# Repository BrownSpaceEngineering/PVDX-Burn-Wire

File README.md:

# BurnWire

Burn-wire release board for the PVDX CubeSat. Generates a constant current of 1.6A through a nichrome wire to sever the retention line holding deployable camera arm in its stowed position.

## Status
- Design phase: manufactured (rev-3.1 sent to fab 2026-08-22)
- Current rev: rev-3.1
- Contributors: Atharv Chowdhary, Nick Cavallo, Jayla Hsiung, Emily Zhang, Kelly Lin, Natalie Cavallo, Misha Zinchuk

## System overview

BurnWire was originally forked from another team's Altium-designed board and imported into KiCad, which is the source of most of the quirks documented below. 

**WIP**
Known components on the board (confirmed via schematic/PCB library references, not yet mapped to a full circuit description — fill in as this gets documented properly):

- **ADP2303ARDZ** — synchronous step-down switching regulator. Per standing design notes, this part needs a Schottky diode (e.g. BAT54, here likely the placed **B330B-13-F**) from V_in to the BST pin to prevent bootstrap collapse at 5V input (datasheet Figure 48) — worth confirming this placement is present and correctly oriented.
- **B330B-13-F** — Schottky diode, SMB package (3 footprint variants exist in `libs/footprints.pretty/`: base, `-M`, `-L`; the placed instance uses `-L`).
- **IND_NLV32T_TDK** (TDK NLV32T-3R3J-EF, 3.3µH) and **Bourns SRN6045** — two inductor footprints present; [confirm: both used in the regulator stage, or does one serve the burn-wire drive circuit?]
- **JST B6B-XH-A** 6-pin connector — external interface (power / command / burn-wire line — confirm pinout).
- 0.25Ω 3W power resistor (2512/2010 footprint) — likely current-sense or burn-wire load-adjacent; confirm function.
- Standard passives: 0603/0805 resistors, 0603 100nF decoupling caps, WCAP-ASLI 5x5.5mm bulk electrolytic.
- Test points inherited from the original board's library (`PowerManagmentBoard_V4.0:TP` nickname — currently orphaned, see Open Items).

### Repo layout
```
BurnWire/
├── BurnWire.kicad_pro / .kicad_sch / .kicad_pcb / .step
├── LTSpice_burnWire.asc
├── fp-lib-table, sym-lib-table
├── libs/
│   ├── footprints.pretty/
│   └── symbols/
└── manufacturing/
    └── rev-1_2026-08-22/
        └── gerbers/
```
No schematics/, spice/, or tools/ directories — the LTSpice simulation is currently stored at the repository root as LTSpice_burnWire.asc.

## Key design notes
- **Inherited from Altium, not yet fully re-linked in KiCad.** Nearly every custom part on the schematic (`Burn Wire Dev Board-altium-import:*`, `Burn Wire Dev Board:root_N_*`, `PowerManagmentBoard_V4.0:*`) has no corresponding entry in `sym-lib-table`. The schematic still opens and renders correctly because KiCad caches each symbol's full geometry inline at placement time — `sym-lib-table` is only consulted when re-editing or re-placing a symbol. Don't take "it opens fine" as evidence the library links are healthy.
- **PCB layer names are non-standard**, carried over from the Altium import (e.g. `Mechanical 1/5/7/13/15`, `User.2/3/4` instead of KiCad's standard `Margin`/`User.Comments`/etc.). Not remapped in this reorg — flagged as a full production-file redo for later, out of scope for repo hygiene.
- **ADP2303 bootstrap diode** — see System overview above; this is a known failure mode for this regulator at 5V input, worth double-checking against the datasheet if this board is ever re-spun.
- `libs/symbols/` now holds four properly filed vendor symbols (B330B-13-F, B6B-XH-A_LF__SN_, NLV32T-3R3J-EF, WCAP-ASLI_5X5.5), but **none are currently referenced by the schematic** — the placed parts use generic `Device:`/`Connector:` symbols instead. These are available for future use, not currently wired in.

## Simulations
- `LTSpice_burnWire.asc` — LTSpice simulation of the burn-wire constant-current regulator.

## Manufacturing history
| Rev | Date | Notes | Location |
|-----|------|-------|----------|
| 3.1 | 2026-08-22 | First fab | `manufacturing/rev-1_2026-08-22/gerbers/` |

## Open items / TBD
- PCB layer names still reflect the Altium import (`Mechanical 1/5/7/13/15`, `User.2/3/4`) — needs remapping to standard KiCad layers as part of a full production-file redo.
- `burn_wire:CR_SMB_320-345BE_DIO-L` and `burn_wire:IND_BOURNS_SRN6045` footprint nicknames on the PCB aren't yet re-linked to the `footprints` library in `fp-lib-table` — the backing files exist in `libs/footprints.pretty/` now, they just need the reference updated.
- `Burn Wire Dev Board:0603` and `PowerManagmentBoard_V4.0:TP` footprint nicknames have no backing file anywhere in the repo — genuinely missing, not just unlinked.
- Most schematic symbols are unlinked from `sym-lib-table` (see Key design notes) — re-linking or rebuilding these is a real schematic-level task, not a file move.
- The placed `burn_wire:CR_SMB_320-345BE_DIO-L` instance has a pad offset that doesn't cleanly match either library copy of that footprint (hand-nudged geometry) — worth a visual QC pass against the fabbed rev-1 board.

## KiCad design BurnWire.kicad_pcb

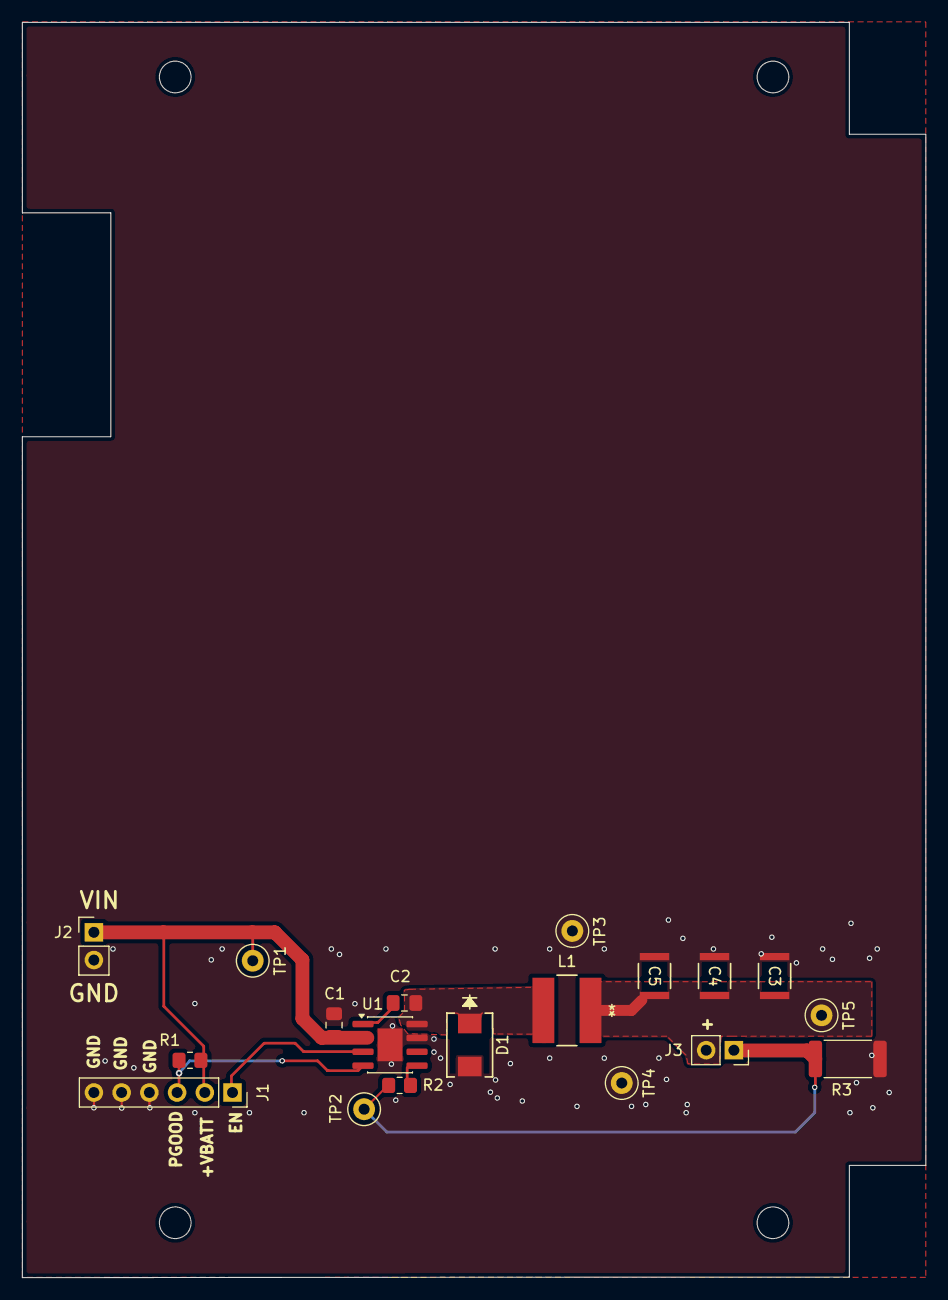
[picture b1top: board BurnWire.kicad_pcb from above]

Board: 2 copper layers, 82.8 x 115.0 mm, 19 parts (0 on the bottom side), 9 nets.

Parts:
C1: 22u; C_0805_2012Metric_Pad1.18x1.45mm_HandSolder
C2: 0.1u; C_0805_2012Metric_Pad1.18x1.45mm_HandSolder
C3, C4, C5: 47uF; CAP_GRM_32E_MUR
D1: B330B-F; CR_SMB_320-345BE_DIO-L
J1: Conn_01x06_Pin; PinSocket_1x06_P2.54mm_Vertical
J2: Conn_01x02_Pin; PinHeader_1x02_P2.54mm_Vertical
J3: Conn_01x02_Pin; PinSocket_1x02_P2.54mm_Vertical
L1: 3.3u; IND_BOURNS_SRN6045
R1, R2: 10k; R_0805_2012Metric_Pad1.20x1.40mm_HandSolder
R3: 0.5R; R_2512_6332Metric
TP1, TP2, TP3, TP4, TP5: TP; TestPoint_Loop_D1.80mm_Drill1.0mm_Beaded
U1: ADP2303ARDZ; SOIC-8-1EP_3.9x4.9mm_P1.27mm_EP2.29x3mm

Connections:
+VBATT: C1.1, J1.2, J2.1, R1.2, TP1.1 (1_1), U1.2 (Vin)
/BURN_NEG: J3.1, R2.2, R3.2, TP2.1 (1_1)
/BURN_POS: C3.2, C4.2, C5.2, J3.2, L1.1, TP5.1 (1_1)
/ENABLE: J1.1, U1.3 (EN)
/FB: R2.1, U1.5 (FB)
/PGOOD: J1.3, R1.1, U1.4 (PGOOD)
GND: C1.2, C3.1, C4.1, C5.1, D1.2 (A), J1.4, J1.5, J1.6, J2.2, R3.1, TP3.1 (1_1), TP4.1 (1_1), U1.7 (GND), U1.9 (PADGND)
unnamed: C2.1, D1.1 (K), L1.2, U1.8 (SW)
unnamed: C2.2, U1.1 (BST)

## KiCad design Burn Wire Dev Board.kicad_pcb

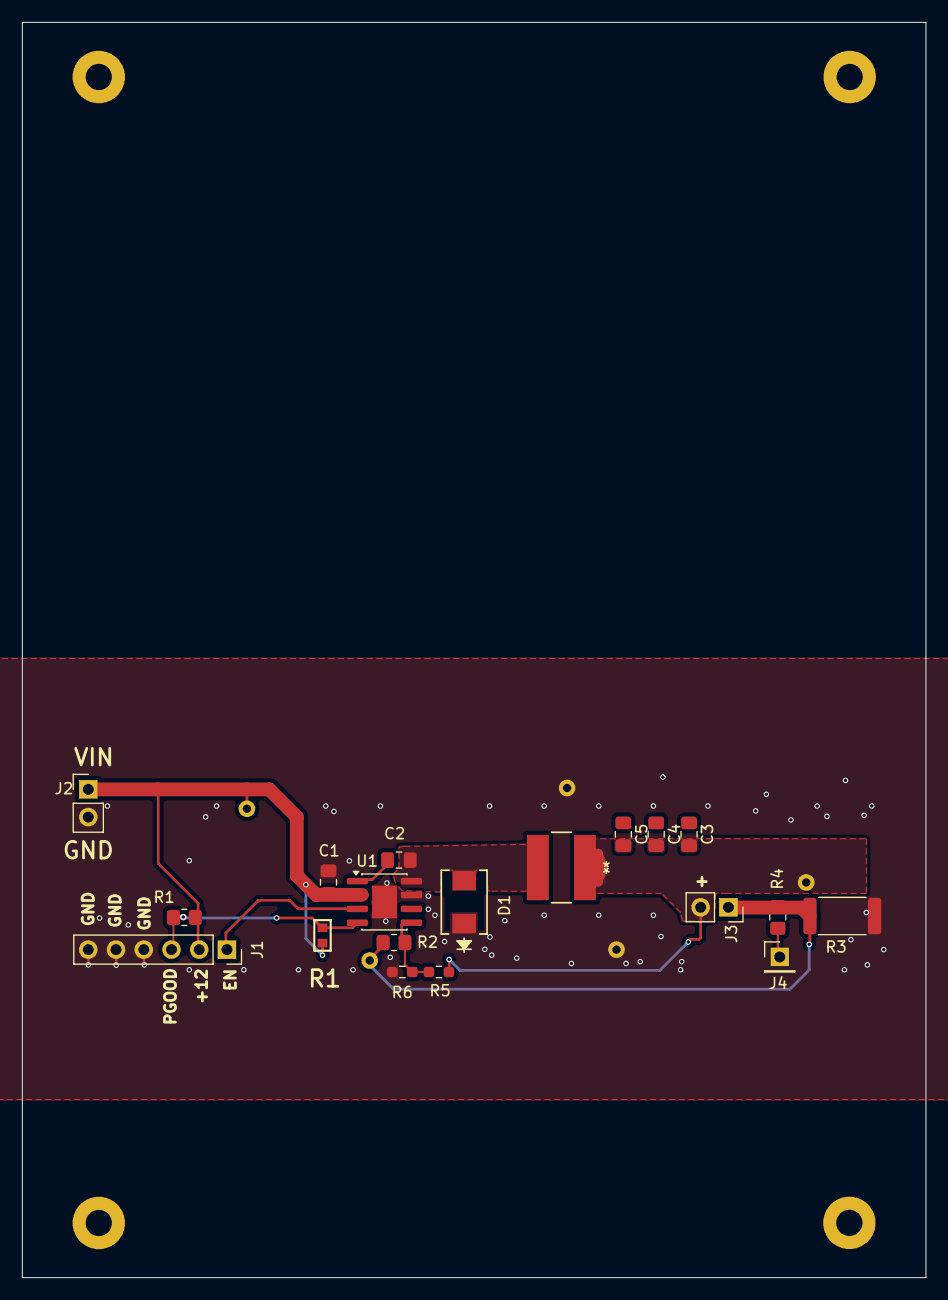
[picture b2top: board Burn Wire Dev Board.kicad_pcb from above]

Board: 2 copper layers, 82.8 x 115.0 mm, 28 parts (0 on the bottom side), 10 nets.

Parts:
*1, *2, *3, *3#2: M2 Mounting; M2 Screws
C1: 22uF; C_0805_2012Metric_Pad1.18x1.45mm_HandSolder
C2: 0.1uF; C_0805_2012Metric_Pad1.18x1.45mm_HandSolder
C3, C4, C5: 47 uF; C_0805_2012Metric_Pad1.18x1.45mm_HandSolder
D1: D_Schottky; CR_SMB_320-345BE_DIO-L
J1: Conn_01x06_Pin; PinSocket_1x06_P2.54mm_Vertical
J2: 282834-2; PinHeader_1x02_P2.54mm_Vertical
J3: Conn_01x02_Pin; PinSocket_1x02_P2.54mm_Vertical
J4: Conn_01x01_Pin; PinHeader_1x01_P2.54mm_Vertical
L1: 6.8 UH; IND_BOURNS_SRN6045
R1: 10K; 0603
R1#2, R2: 10K; R_0805_2012Metric_Pad1.20x1.40mm_HandSolder
R3: 0.25R; R_2512_6332Metric
R4: 1k; R_0805_2012Metric_Pad1.20x1.40mm_HandSolder
R5, R6: 0R; R_0603_1608Metric_Pad0.98x0.95mm_HandSolder
TP1, TP2, TP3, TP4, TP5: TP
U1: ADP2303ARDZ; SOIC-8-1EP_3.9x4.9mm_P1.27mm_EP2.29x3mm

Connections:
+VBATT: C1.1, J1.2, J2.1, R1.2, R1#2.2, TP2.1, U1.2 (Vin)
/BURN_NEG: J3.1, R2.2, R3.2, R4.1, TP3.1
/BURN_POS: C3.1, C4.1, C5.1, J3.2, R5.2, TP1.1
/ENABLE: J1.1, U1.3 (EN)
GND: *1.1, C1.2, C3.2, C4.2, C5.2, D1.1 (K), J1.4, J1.5, J1.6, J2.2, R3.1, R6.1, TP4.1, TP5.1, U1.7 (GND), U1.9 (PADGND)
unnamed: C2.1, D1.2 (A), L1.2 (2_2), U1.8 (SW)
unnamed: C2.2, U1.1 (BST)
unnamed: R2.1, R5.1, R6.2, U1.5 (FB)
PGOOD: J1.3, R1.1, R1#2.1, U1.4 (PGOOD)
TO_COMPUTE: J4.1 (Pin_1_1), R4.2

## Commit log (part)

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2025-11-02 Initial commit of KiCAD files for burn wire circuit
2025-11-02 completed schematic, added most footprints
2025-11-02 Added footprint libraries, reorganized imported components, Assigned footprints
2025-11-04 imported more footprints, completed layout
2025-11-16 done
2025-11-16 Add design rules to layout
2025-11-20 reworked most of the layout
2025-11-23 finished routing
2025-11-26 burnwire design complete
2026-01-30 reduced number of vias
2026-02-06 fixed some DRC violations
2026-02-06 unflipped version; passes DRC
2026-02-08 done layout
2026-02-08 optimized layout
2026-02-08 generated gerber
2026-02-13 redid layout
2026-02-22 started one layer
2026-02-22 finished one-layer layout
2026-02-22 done onelayer
2026-02-23 Edit via size, connect Vout
2026-03-08 Changes for manufacturing
2026-04-05 added burnwire final ltspice
2026-04-05 Add new inductor component
2026-04-05 updated schematic
2026-04-06 Polished schema w/ labels, test points; updated layout for new Vout->FB VDivider
2026-04-06 fixed R3 to correct value 100K in layout
2026-04-07 Modified layout for more space
2026-04-07 done burnwire
2026-04-07 pushed gerber files
2026-04-21 updated L1 value in layout
2026-05-03 added kiran schematic
